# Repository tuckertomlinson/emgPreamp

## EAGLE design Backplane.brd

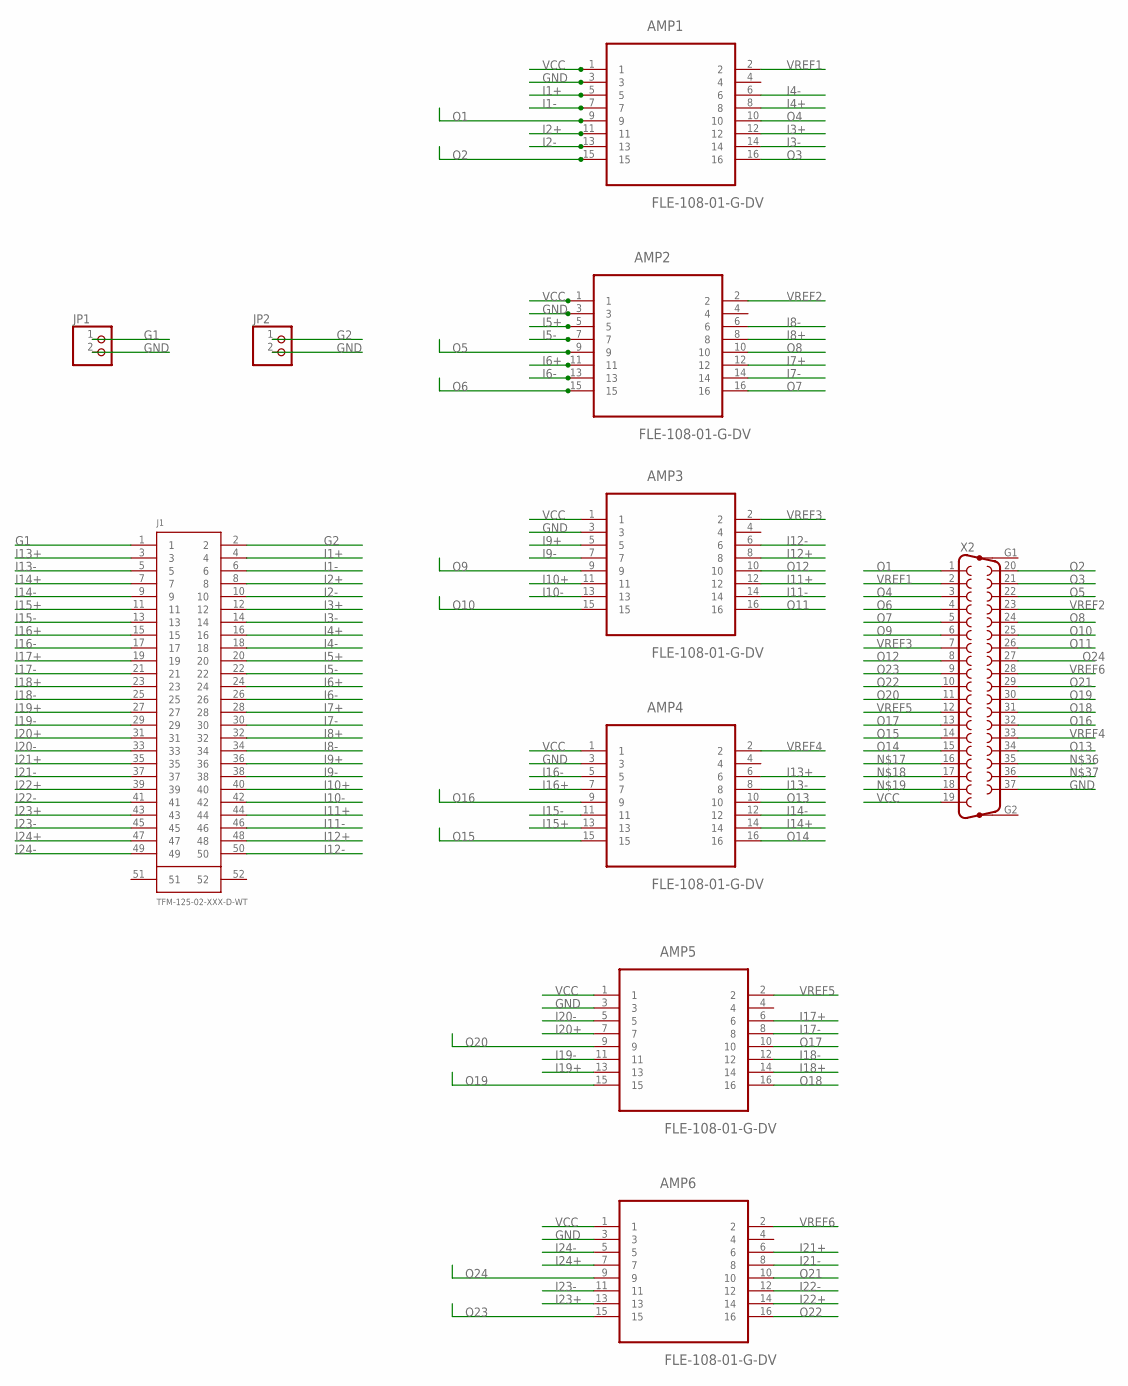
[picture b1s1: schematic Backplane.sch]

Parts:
AMP1, AMP2, AMP3, AMP4, AMP5, AMP6: FLE-108-01-G-DV; SAMTEC_FLE-108-01-G-DV
J1: TFM-125-02-XXX-D-WT
JP1, JP2: PINHD-1X2; 1X02
X2: F37HP

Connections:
G1: J1.1, JP1.1
G2: J1.2, JP2.1
GND: AMP1.3, AMP2.3, AMP3.3, AMP4.3, AMP5.3, AMP6.3, JP1.2, JP2.2, X2.37
I1+: AMP1.5, J1.4
I1-: AMP1.7, J1.6
I2+: AMP1.11, J1.8
I2-: AMP1.13, J1.10
I3+: AMP1.12, J1.12
I3-: AMP1.14, J1.14
I4+: AMP1.8, J1.16
I4-: AMP1.6, J1.18
I5+: AMP2.5, J1.20
I5-: AMP2.7, J1.22
I6+: AMP2.11, J1.24
I6-: AMP2.13, J1.26
I7+: AMP2.12, J1.28
I7-: AMP2.14, J1.30
I8+: AMP2.8, J1.32
I8-: AMP2.6, J1.34
I9+: AMP3.5, J1.36
I9-: AMP3.7, J1.38
I10+: AMP3.11, J1.40
I10-: AMP3.13, J1.42
I11+: AMP3.12, J1.44
I11-: AMP3.14, J1.46
I12+: AMP3.8, J1.48
I12-: AMP3.6, J1.50
I13+: AMP4.6, J1.3
I13-: AMP4.8, J1.5
I14+: AMP4.14, J1.7
I14-: AMP4.12, J1.9
I15+: AMP4.13, J1.11
I15-: AMP4.11, J1.13
I16+: AMP4.7, J1.15
I16-: AMP4.5, J1.17
I17+: AMP5.6, J1.19
I17-: AMP5.8, J1.21
I18+: AMP5.14, J1.23
I18-: AMP5.12, J1.25
I19+: AMP5.13, J1.27
I19-: AMP5.11, J1.29
I20+: AMP5.7, J1.31
I20-: AMP5.5, J1.33
I21+: AMP6.6, J1.35
I21-: AMP6.8, J1.37
I22+: AMP6.14, J1.39
I22-: AMP6.12, J1.41
I23+: AMP6.13, J1.43
I23-: AMP6.11, J1.45
I24+: AMP6.7, J1.47
I24-: AMP6.5, J1.49
O1: AMP1.9, X2.1
O2: AMP1.15, X2.20
O3: AMP1.16, X2.21
O4: AMP1.10, X2.3
O5: AMP2.9, X2.22
O6: AMP2.15, X2.4
O7: AMP2.16, X2.5
O8: AMP2.10, X2.24
O9: AMP3.9, X2.6
O10: AMP3.15, X2.25
O11: AMP3.16, X2.26
O12: AMP3.10, X2.8
O13: AMP4.10, X2.34
O14: AMP4.16, X2.15
O15: AMP4.15, X2.14
O16: AMP4.9, X2.32
O17: AMP5.10, X2.13
O18: AMP5.16, X2.31
O19: AMP5.15, X2.30
O20: AMP5.9, X2.11
O21: AMP6.10, X2.29
O22: AMP6.16, X2.10
O23: AMP6.15, X2.9
O24: AMP6.9, X2.27
VCC: AMP1.1, AMP2.1, AMP3.1, AMP4.1, AMP5.1, AMP6.1, X2.19
VREF1: AMP1.2, X2.2
VREF2: AMP2.2, X2.23
VREF3: AMP3.2, X2.7
VREF4: AMP4.2, X2.33
VREF5: AMP5.2, X2.12
VREF6: AMP6.2, X2.28

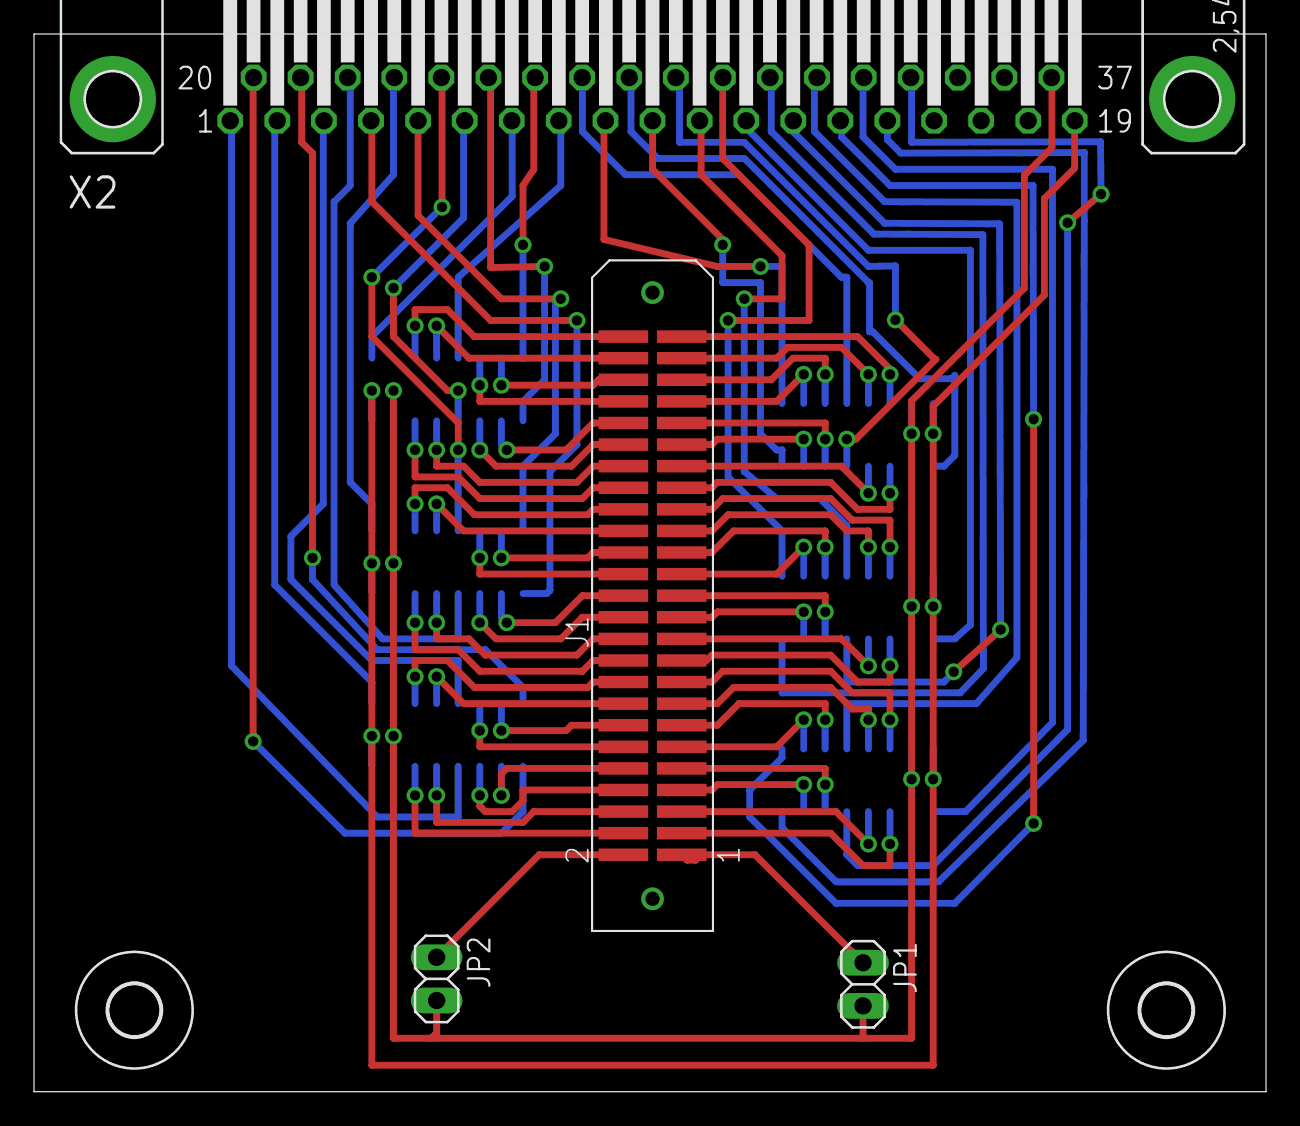
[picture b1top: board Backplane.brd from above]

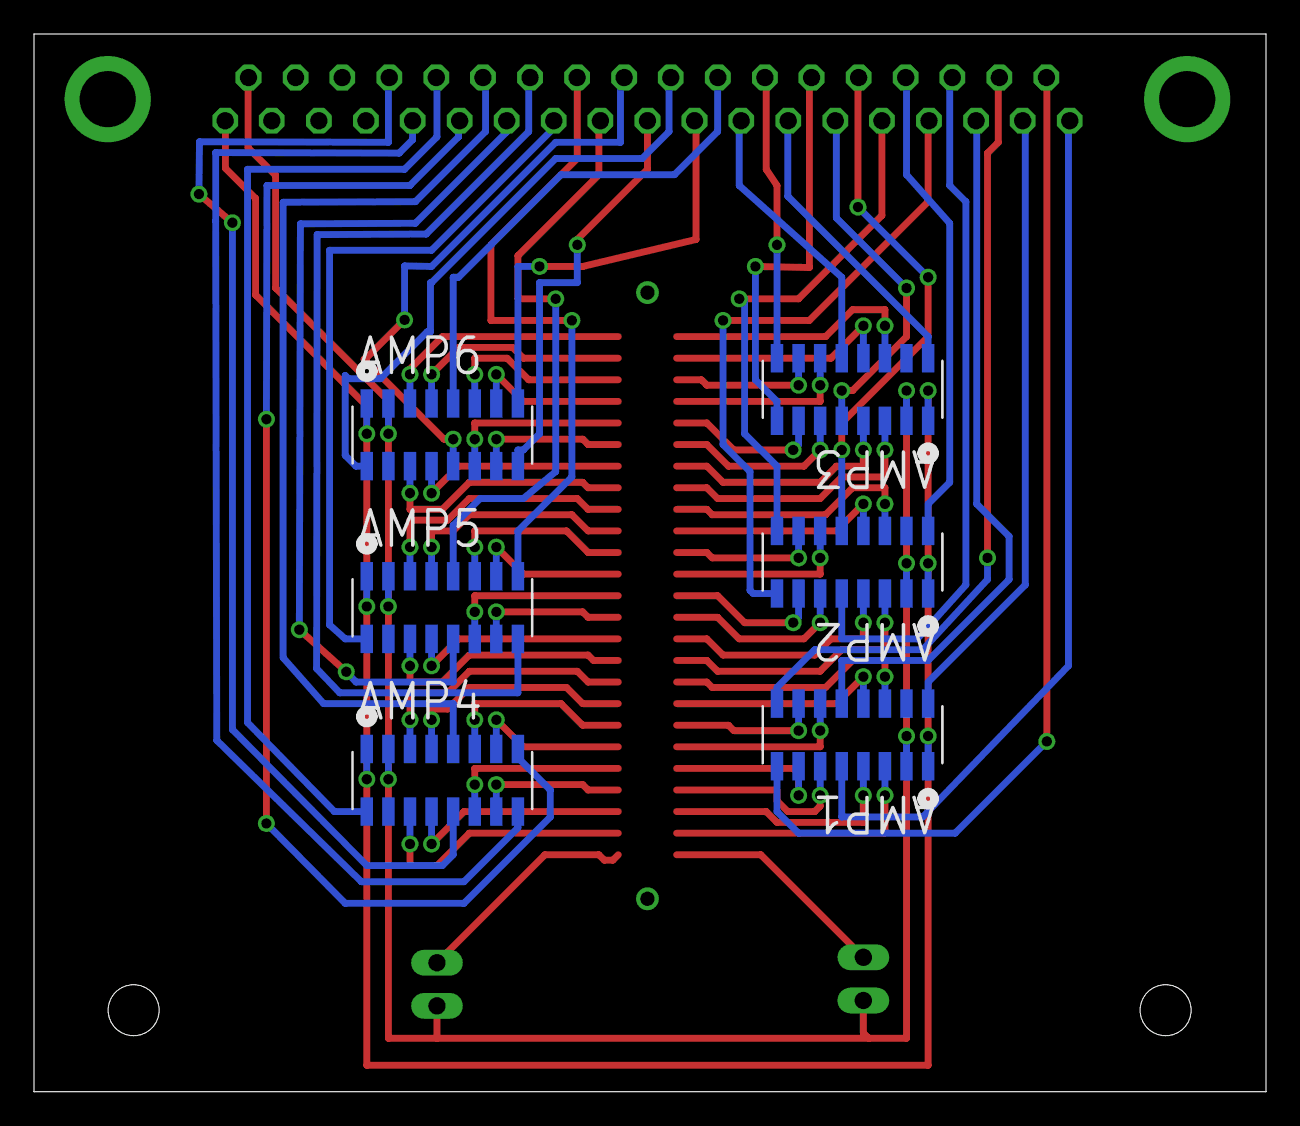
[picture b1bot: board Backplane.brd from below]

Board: 2 copper layers, 72.5 x 62.2 mm, 12 parts (6 on the bottom side), 82 nets.

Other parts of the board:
U$1, U$2: 3,0

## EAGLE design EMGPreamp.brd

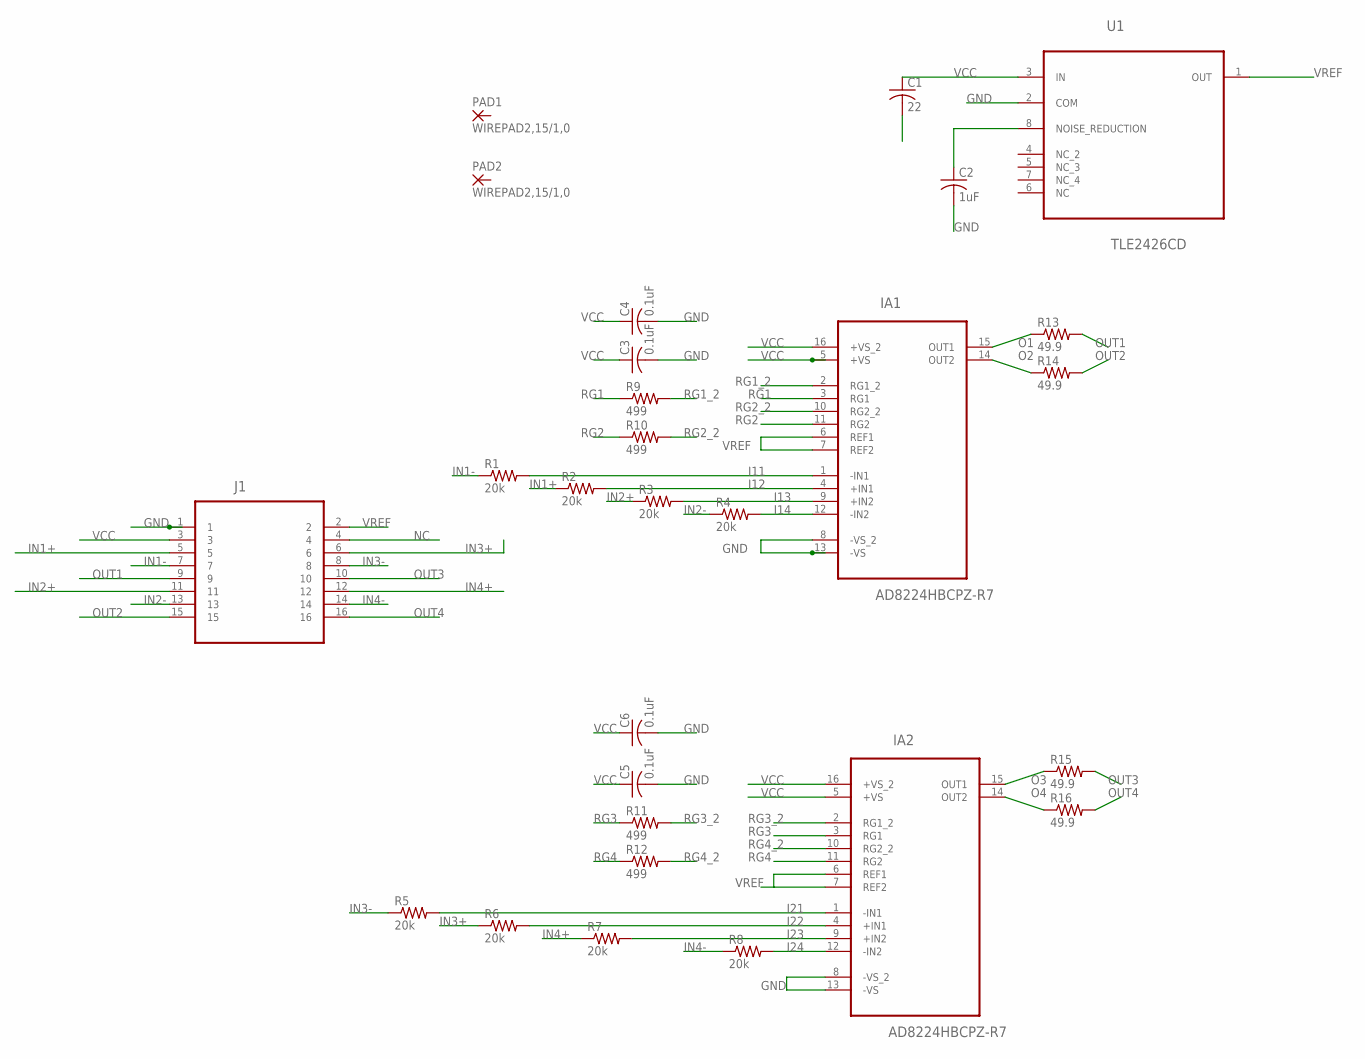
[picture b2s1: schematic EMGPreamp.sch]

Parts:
C1: 22; C0805
C2: 1uF; C0805
C3, C4, C5, C6: 0.1uF; C0805
IA1, IA2: AD8224HBCPZ-R7; QFN65P400X400X100-16N
J1: FTSH-108-01-L-MT; FTSH-108-1-L-MT
PAD1, PAD2: WIREPAD2,15/1,0; 2,15/1,0
R1, R2, R3, R4, R5, R6, R7, R8: 20k; R0805
R9, R10, R11, R12: 499; R0805
R13, R14, R15, R16: 49.9; R0805
U1: TLE2426CD; SOIC127P600X175-8N

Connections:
GND: C1.2, C2.2, C3.2, C4.2, C5.2, C6.2, IA1.8 (-VS_2), IA1.13 (-VS), IA2.8 (-VS_2), IA2.13 (-VS), J1.1, U1.2 (COM)
I11: IA1.1 (-IN1), R1.2
I12: IA1.4 (+IN1), R2.2
I13: IA1.9 (+IN2), R3.2
I14: IA1.12 (-IN2), R4.2
I21: IA2.1 (-IN1), R5.2
I22: IA2.4 (+IN1), R6.2
I23: IA2.9 (+IN2), R7.2
I24: IA2.12 (-IN2), R8.2
IN1+: J1.5, R2.1
IN1-: J1.7, R1.1
IN2+: J1.11, R3.1
IN2-: J1.13, R4.1
IN3+: J1.6, R6.1
IN3-: J1.8, R5.1
IN4+: J1.12, R7.1
IN4-: J1.14, R8.1
unnamed: C2.1, U1.8 (NOISE_REDUCTION)
NC: J1.4
O1: IA1.15 (OUT1), R13.1
O2: IA1.14 (OUT2), R14.1
O3: IA2.15 (OUT1), R15.1
O4: IA2.14 (OUT2), R16.1
OUT1: J1.9, R13.2
OUT2: J1.15, R14.2
OUT3: J1.10, R15.2
OUT4: J1.16, R16.2
RG1: IA1.3 (RG1), R9.1
RG1_2: IA1.2 (RG1_2), R9.2
RG2: IA1.11 (RG2), R10.1
RG2_2: IA1.10 (RG2_2), R10.2
RG3: IA2.3 (RG1), R11.1
RG3_2: IA2.2 (RG1_2), R11.2
RG4: IA2.11 (RG2), R12.1
RG4_2: IA2.10 (RG2_2), R12.2
VCC: C1.1, C3.1, C4.1, C5.1, C6.1, IA1.5 (+VS), IA1.16 (+VS_2), IA2.5 (+VS), IA2.16 (+VS_2), J1.3, U1.3 (IN)
VREF: IA1.6 (REF1), IA1.7 (REF2), IA2.6 (REF1), IA2.7 (REF2), J1.2, U1.1 (OUT)

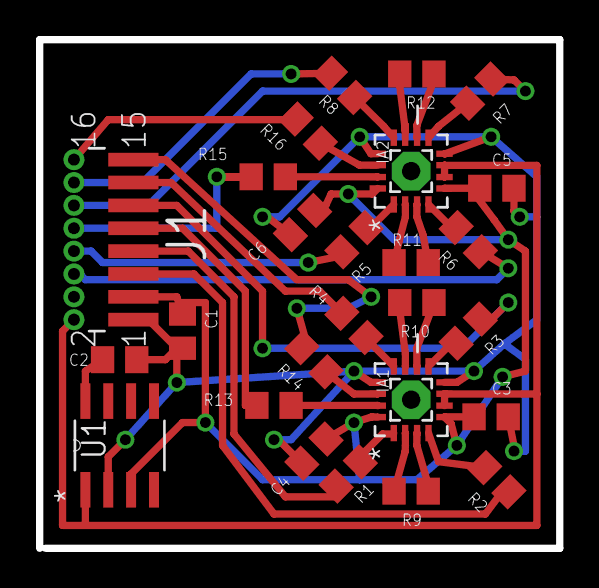
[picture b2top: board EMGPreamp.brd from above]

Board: 2 copper layers, 28.9 x 28.3 mm, 28 parts (0 on the bottom side), 36 nets.

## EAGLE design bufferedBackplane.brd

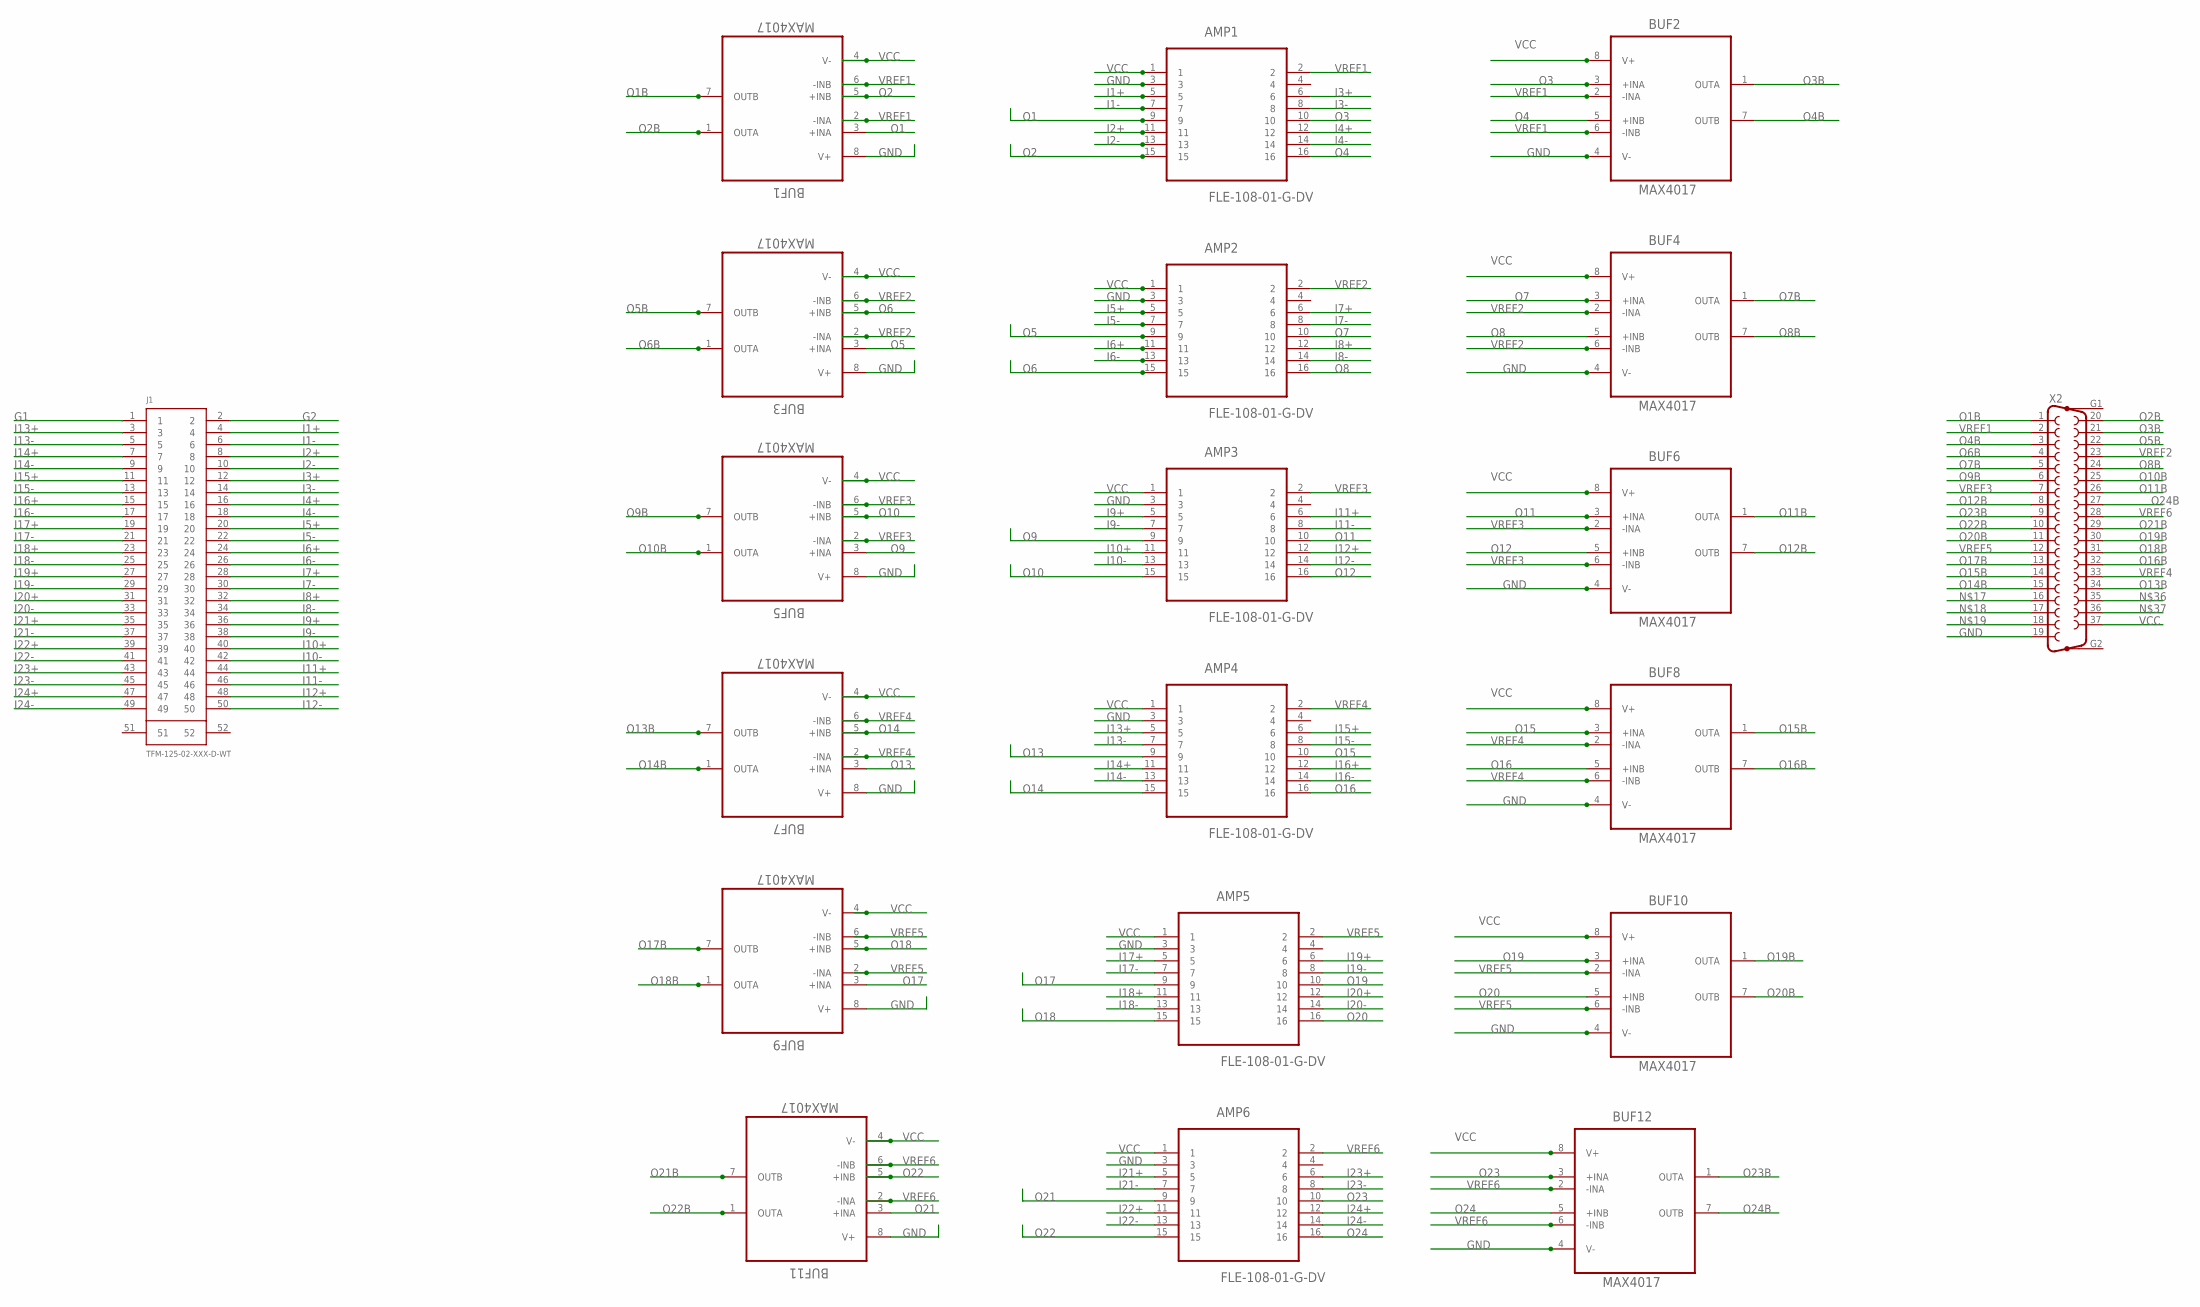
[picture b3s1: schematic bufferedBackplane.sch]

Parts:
AMP1, AMP2, AMP3, AMP4, AMP5, AMP6: FLE-108-01-G-DV; SAMTEC_FLE-108-01-G-DV
BUF1, BUF2, BUF3, BUF4, BUF5, BUF6, BUF7, BUF8, BUF9, BUF10, BUF11, BUF12: MAX4017
J1: TFM-125-02-XXX-D-WT
X2: F37HP

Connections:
G1: J1.1
G2: J1.2
GND: AMP1.3, AMP2.3, AMP3.3, AMP4.3, AMP5.3, AMP6.3, BUF1.8 (V+), BUF2.4 (V-), BUF3.8 (V+), BUF4.4 (V-), BUF5.8 (V+), BUF6.4 (V-), BUF7.8 (V+), BUF8.4 (V-), BUF9.8 (V+), BUF10.4 (V-), BUF11.8 (V+), BUF12.4 (V-), X2.19
I1+: AMP1.5, J1.4
I1-: AMP1.7, J1.6
I2+: AMP1.11, J1.8
I2-: AMP1.13, J1.10
I3+: AMP1.6, J1.12
I3-: AMP1.8, J1.14
I4+: AMP1.12, J1.16
I4-: AMP1.14, J1.18
I5+: AMP2.5, J1.20
I5-: AMP2.7, J1.22
I6+: AMP2.11, J1.24
I6-: AMP2.13, J1.26
I7+: AMP2.6, J1.28
I7-: AMP2.8, J1.30
I8+: AMP2.12, J1.32
I8-: AMP2.14, J1.34
I9+: AMP3.5, J1.36
I9-: AMP3.7, J1.38
I10+: AMP3.11, J1.40
I10-: AMP3.13, J1.42
I11+: AMP3.6, J1.44
I11-: AMP3.8, J1.46
I12+: AMP3.12, J1.48
I12-: AMP3.14, J1.50
I13+: AMP4.5, J1.3
I13-: AMP4.7, J1.5
I14+: AMP4.11, J1.7
I14-: AMP4.13, J1.9
I15+: AMP4.6, J1.11
I15-: AMP4.8, J1.13
I16+: AMP4.12, J1.15
I16-: AMP4.14, J1.17
I17+: AMP5.5, J1.19
I17-: AMP5.7, J1.21
I18+: AMP5.11, J1.23
I18-: AMP5.13, J1.25
I19+: AMP5.6, J1.27
I19-: AMP5.8, J1.29
I20+: AMP5.12, J1.31
I20-: AMP5.14, J1.33
I21+: AMP6.5, J1.35
I21-: AMP6.7, J1.37
I22+: AMP6.11, J1.39
I22-: AMP6.13, J1.41
I23+: AMP6.6, J1.43
I23-: AMP6.8, J1.45
I24+: AMP6.12, J1.47
I24-: AMP6.14, J1.49
O1: AMP1.9, BUF1.3 (+INA)
O1B: BUF1.7 (OUTB), X2.1
O2: AMP1.15, BUF1.5 (+INB)
O2B: BUF1.1 (OUTA), X2.20
O3: AMP1.10, BUF2.3 (+INA)
O3B: BUF2.1 (OUTA), X2.21
O4: AMP1.16, BUF2.5 (+INB)
O4B: BUF2.7 (OUTB), X2.3
O5: AMP2.9, BUF3.3 (+INA)
O5B: BUF3.7 (OUTB), X2.22
O6: AMP2.15, BUF3.5 (+INB)
O6B: BUF3.1 (OUTA), X2.4
O7: AMP2.10, BUF4.3 (+INA)
O7B: BUF4.1 (OUTA), X2.5
O8: AMP2.16, BUF4.5 (+INB)
O8B: BUF4.7 (OUTB), X2.24
O9: AMP3.9, BUF5.3 (+INA)
O9B: BUF5.7 (OUTB), X2.6
O10: AMP3.15, BUF5.5 (+INB)
O10B: BUF5.1 (OUTA), X2.25
O11: AMP3.10, BUF6.3 (+INA)
O11B: BUF6.1 (OUTA), X2.26
O12: AMP3.16, BUF6.5 (+INB)
O12B: BUF6.7 (OUTB), X2.8
O13: AMP4.9, BUF7.3 (+INA)
O13B: BUF7.7 (OUTB), X2.34
O14: AMP4.15, BUF7.5 (+INB)
O14B: BUF7.1 (OUTA), X2.15
O15: AMP4.10, BUF8.3 (+INA)
O15B: BUF8.1 (OUTA), X2.14
O16: AMP4.16, BUF8.5 (+INB)
O16B: BUF8.7 (OUTB), X2.32
O17: AMP5.9, BUF9.3 (+INA)
O17B: BUF9.7 (OUTB), X2.13
O18: AMP5.15, BUF9.5 (+INB)
O18B: BUF9.1 (OUTA), X2.31
O19: AMP5.10, BUF10.3 (+INA)
O19B: BUF10.1 (OUTA), X2.30
O20: AMP5.16, BUF10.5 (+INB)
O20B: BUF10.7 (OUTB), X2.11
O21: AMP6.9, BUF11.3 (+INA)
O21B: BUF11.7 (OUTB), X2.29
O22: AMP6.15, BUF11.5 (+INB)
O22B: BUF11.1 (OUTA), X2.10
O23: AMP6.10, BUF12.3 (+INA)
O23B: BUF12.1 (OUTA), X2.9
O24: AMP6.16, BUF12.5 (+INB)
O24B: BUF12.7 (OUTB), X2.27
VCC: AMP1.1, AMP2.1, AMP3.1, AMP4.1, AMP5.1, AMP6.1, BUF1.4 (V-), BUF2.8 (V+), BUF3.4 (V-), BUF4.8 (V+), BUF5.4 (V-), BUF6.8 (V+), BUF7.4 (V-), BUF8.8 (V+), BUF9.4 (V-), BUF10.8 (V+), BUF11.4 (V-), BUF12.8 (V+), X2.37
VREF1: AMP1.2, BUF1.2 (-INA), BUF1.6 (-INB), BUF2.2 (-INA), BUF2.6 (-INB), X2.2
VREF2: AMP2.2, BUF3.2 (-INA), BUF3.6 (-INB), BUF4.2 (-INA), BUF4.6 (-INB), X2.23
VREF3: AMP3.2, BUF5.2 (-INA), BUF5.6 (-INB), BUF6.2 (-INA), BUF6.6 (-INB), X2.7
VREF4: AMP4.2, BUF7.2 (-INA), BUF7.6 (-INB), BUF8.2 (-INA), BUF8.6 (-INB), X2.33
VREF5: AMP5.2, BUF9.2 (-INA), BUF9.6 (-INB), BUF10.2 (-INA), BUF10.6 (-INB), X2.12
VREF6: AMP6.2, BUF11.2 (-INA), BUF11.6 (-INB), BUF12.2 (-INA), BUF12.6 (-INB), X2.28

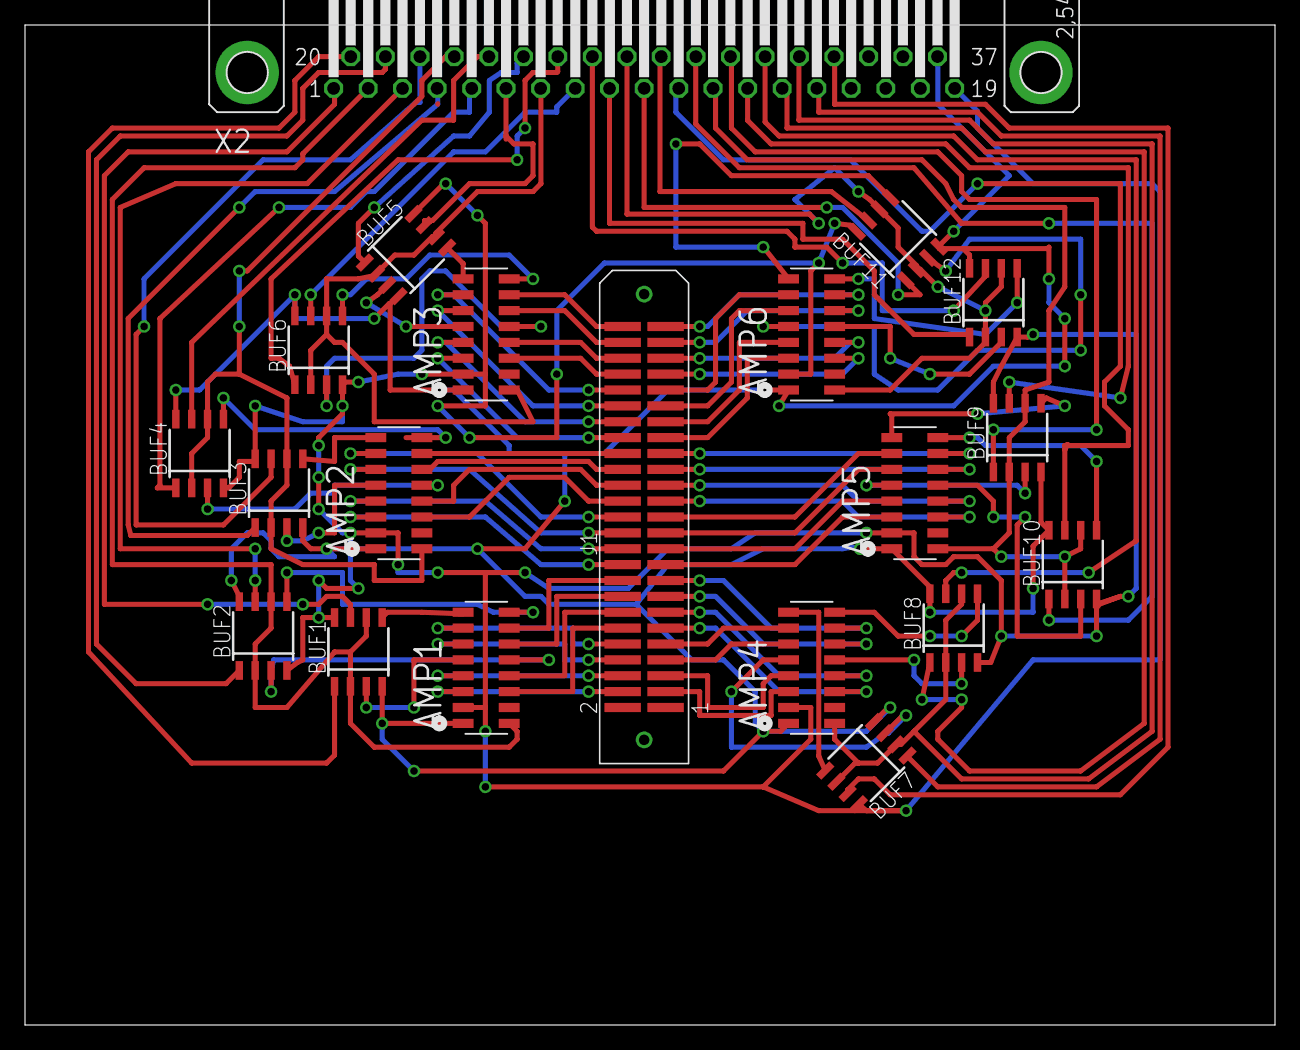
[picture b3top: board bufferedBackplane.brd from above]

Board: 2 copper layers, 100.0 x 80.0 mm, 20 parts (0 on the bottom side), 104 nets.
